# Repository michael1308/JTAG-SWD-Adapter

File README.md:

## JTAG-SWD Adapter

## Description
A general purpose JTAG/SWD adapter board with 20, 10 & 6-pin headers with 2.54mm and 1.27mm pitch.

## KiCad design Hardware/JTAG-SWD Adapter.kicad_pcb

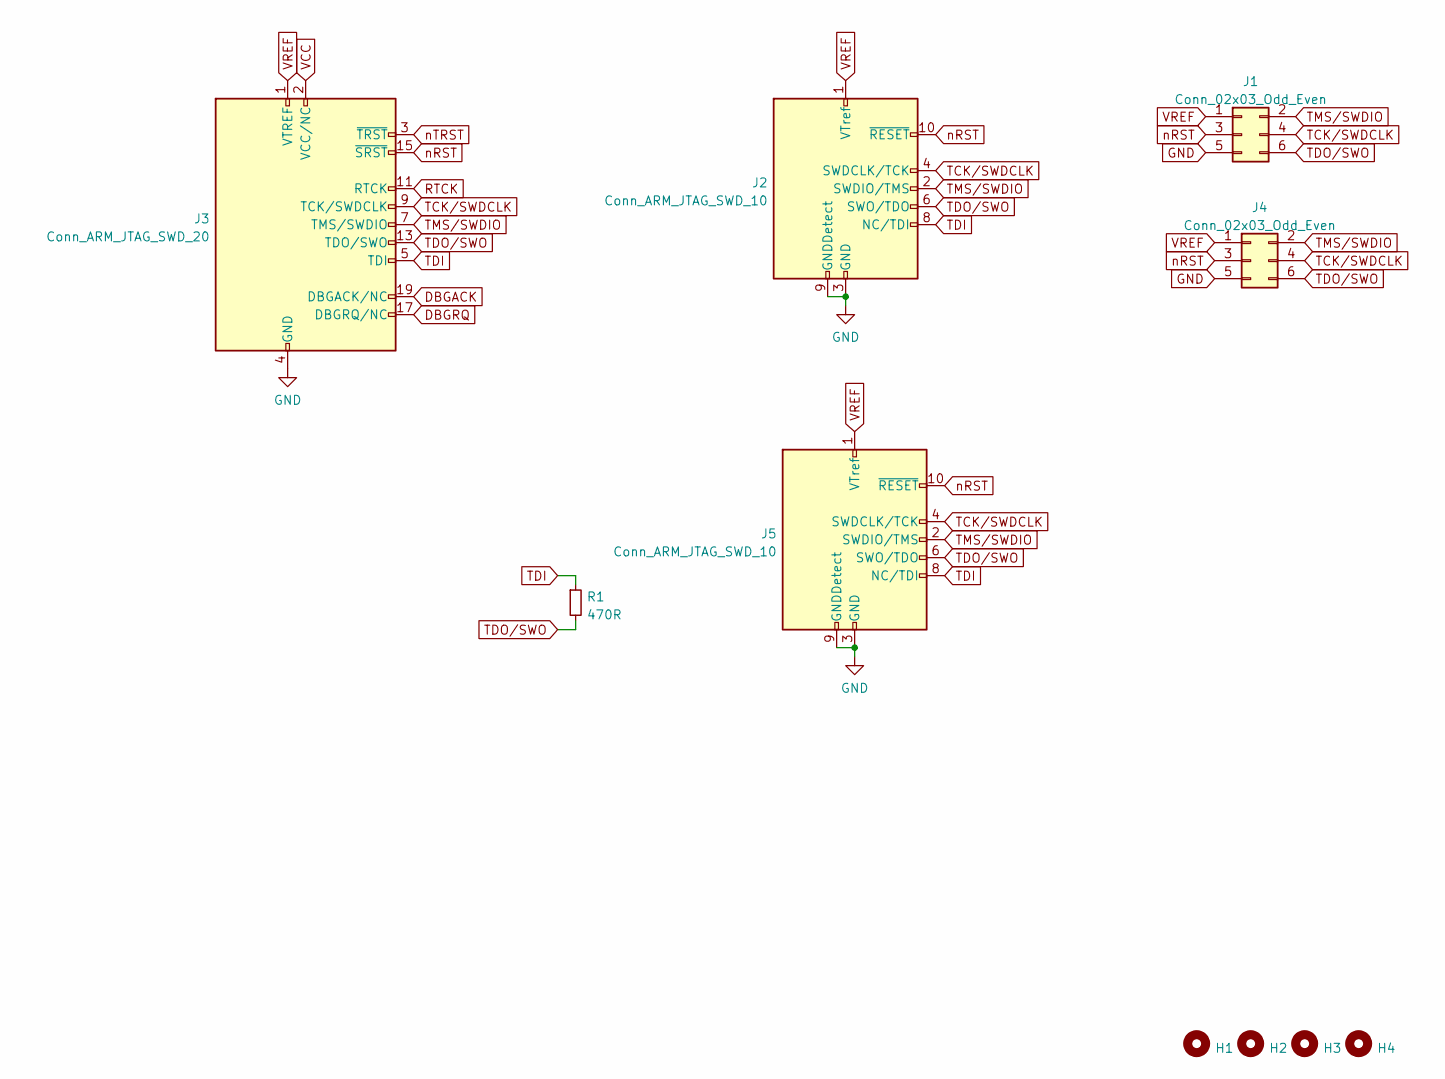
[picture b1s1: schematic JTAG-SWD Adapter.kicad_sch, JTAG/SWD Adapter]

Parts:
H1, H2, H3, H4: MountingHole; MountingHole_3.2mm_M3_Pad_Via
J1: Conn_02x03_Odd_Even; IDC-Header_2x03_P2.54mm_Vertical
J2: Conn_ARM_JTAG_SWD_10; IDC-Header_2x05_P2.54mm_Vertical
J3: Conn_ARM_JTAG_SWD_20; IDC-Header_2x10_P2.54mm_Vertical
J4: Conn_02x03_Odd_Even; IDC_Connector_2x03_P1.27mm
J5: Conn_ARM_JTAG_SWD_10; Connector_IDC_2x05_P1.27
R1: 470R; R_0603_1608Metric

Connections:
DBGACK: J3.19 (DBGACK/NC)
DBGRQ: J3.17 (DBGRQ/NC)
GND: J1.5, J2.3 (GND), J2.5 (GND), J2.9 (GNDDetect), J3.4 (GND), J3.6 (GND), J3.8 (GND), J3.10 (GND), J3.12 (GND), J3.14 (GND), J3.16 (GND), J3.18 (GND), J3.20 (GND), J4.5, J5.3 (GND), J5.5 (GND), J5.9 (GNDDetect)
RTCK: J3.11 (RTCK)
TCK/SWDCLK: J1.4, J2.4 (SWDCLK/TCK), J3.9 (TCK/SWDCLK), J4.4, J5.4 (SWDCLK/TCK)
TDI: J2.8 (NC/TDI), J3.5 (TDI), J5.8 (NC/TDI), R1.1
TDO/SWO: J1.6, J2.6 (SWO/TDO), J3.13 (TDO/SWO), J4.6, J5.6 (SWO/TDO), R1.2
TMS/SWDIO: J1.2, J2.2 (SWDIO/TMS), J3.7 (TMS/SWDIO), J4.2, J5.2 (SWDIO/TMS)
VCC: J3.2 (VCC/NC)
VREF: J1.1, J2.1 (VTref), J3.1 (VTREF), J4.1, J5.1 (VTref)
nRST: J1.3, J2.10 (~RESET), J3.15 (~SRST), J4.3, J5.10 (~RESET)
nTRST: J3.3 (~TRST)

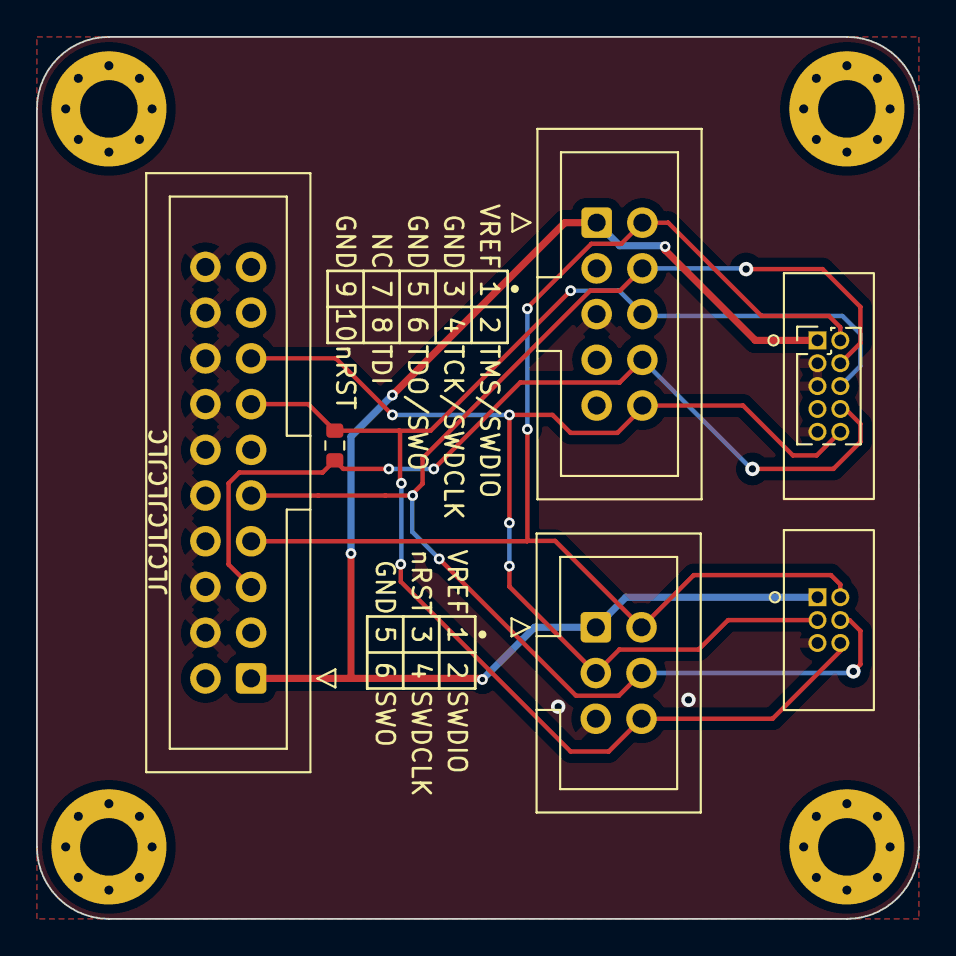
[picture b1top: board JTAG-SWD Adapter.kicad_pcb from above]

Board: 2 copper layers, 49.0 x 49.0 mm, 10 parts (0 on the bottom side), 7 nets.

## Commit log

2023-04-15 v1.0
2024-10-24 add .gitignore
2024-10-24 rename branch
2024-10-24 Drop files from .gitignore
